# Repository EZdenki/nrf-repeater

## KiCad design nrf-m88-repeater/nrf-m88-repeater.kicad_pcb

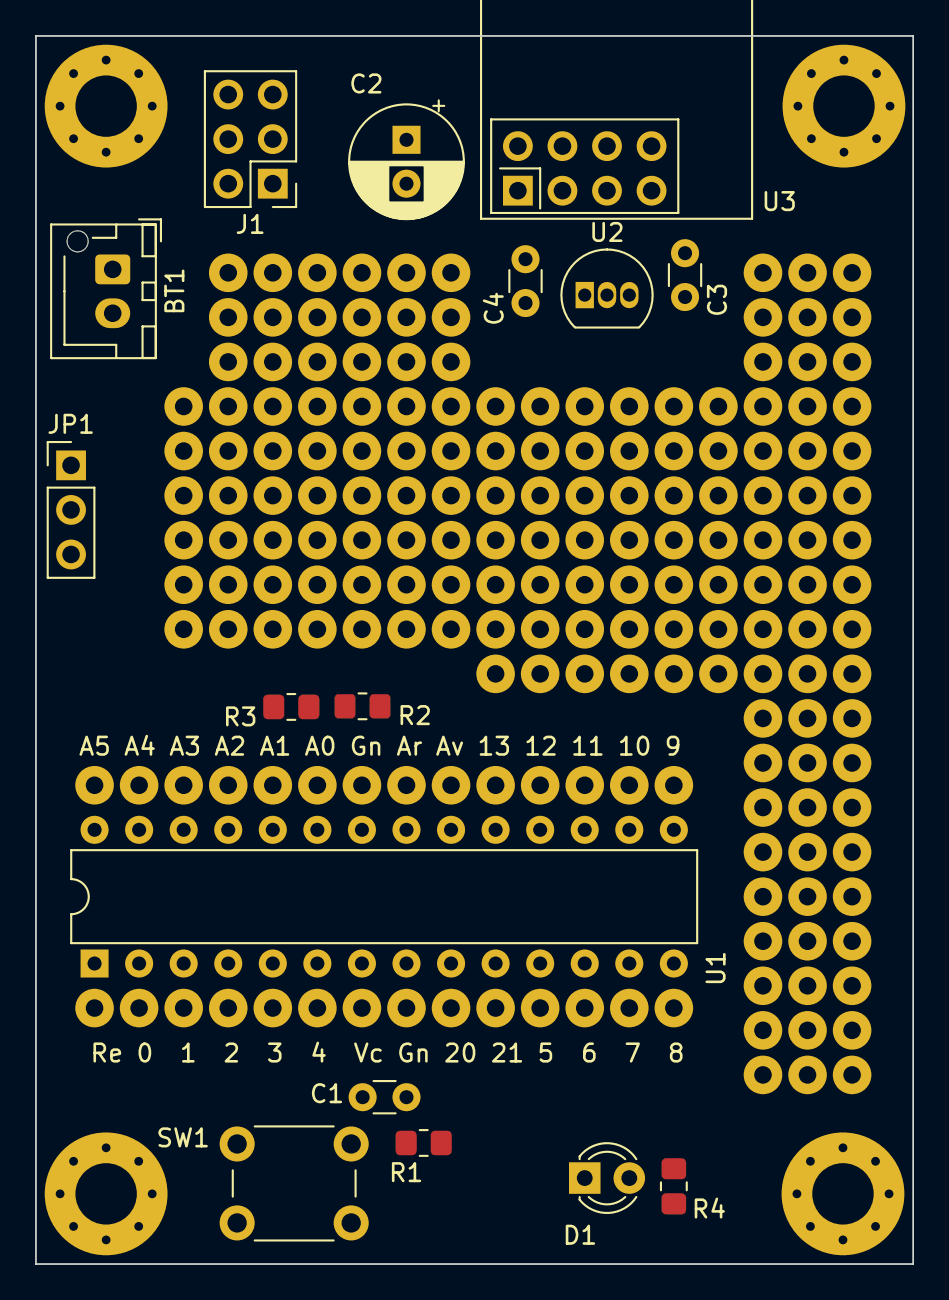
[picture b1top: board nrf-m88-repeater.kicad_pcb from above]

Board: 2 copper layers, 50.0 x 70.0 mm, 20 parts (0 on the bottom side), 13 nets, no tracks yet.

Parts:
BT1: 18650 Battery Holder; JST_XH_B2B-XH-AM_1x02_P2.50mm_Vertical
C1: 100n; C_Disc_D3.0mm_W1.6mm_P2.50mm
C2: 10u; CP_Radial_D6.3mm_P2.50mm
C3: 1u; C_Disc_D3.0mm_W1.6mm_P2.50mm
C4: 2.2u; C_Disc_D3.0mm_W1.6mm_P2.50mm
D1: LED; LED_D3.0mm_FlatTop
H1, H2, H3, H4: MountingHole; MountingHole_3.5mm_Pad_Via
J1: Conn_02x03_Counter_Clockwise; PinHeader_2x03_P2.54mm_Vertical
JP1: PWR Sel.; PinHeader_1x03_P2.54mm_Vertical
R1: 10k; R_0805_2012Metric_Pad1.20x1.40mm_HandSolder
R2: 8.2k; R_0805_2012Metric_Pad1.20x1.40mm_HandSolder
R3: 2.2k; R_0805_2012Metric_Pad1.20x1.40mm_HandSolder
R4: 2k; R_0805_2012Metric_Pad1.20x1.40mm_HandSolder
SW1: RESET; SW_PUSH_6mm
U1: ATmega88; DIP-28_W7.62mm
U2: LP2950-3.3; TO-92_Inline
U3: NRF24L01_Breakout; nRF24L01_Breakout

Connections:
/3.3V: C2.1, C4.2, U2.1 (VO), U3.2 (VCC)
/D8ACT: R4.1, U1.14 (PB0)
/D11MOSI: J1.5, U1.17 (PB3), U3.6 (MOSI)
/D12MISO: J1.1, U1.18 (PB4), U3.7 (MISO)
/D13SCK: J1.2, U1.19 (PB5), U3.5 (SCK)
/D14A0: R2.2, R3.2, U1.23 (PC0)
/ISP_PWR: J1.6, JP1.3 (B)
/RESET: J1.3, SW1.1, U1.1 (~RESET/PC6)
/VCC: C1.1, C3.1, JP1.2 (C), R2.1, U1.7 (VCC), U1.20 (AVCC), U2.3 (VI)
GND: BT1.2 (-), C1.2, C2.2, C3.2, C4.1, D1.1 (K), J1.4, R1.1, R3.1, U1.8 (GND), U1.22 (GND), U2.2 (GND), U3.1 (GND)
unnamed: BT1.1 (+), JP1.1 (A)
unnamed: D1.2 (A), R4.2
unnamed: R1.2, SW1.2

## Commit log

2024-05-07 Ver 1.0
2024-05-08 DIY Version 2
2024-05-13 Repeter V3 Commit
2024-05-22 Added transmitter
2024-05-26 Added V1.3 for Battery monitor
2024-05-26 Fixed up V1.3
2024-05-27 Full Receiver Protoboard V1
2024-05-29 Updated DHT11 wiring
2024-06-14 Updated Receiver V1.2 to add volume and backlight control.
2024-06-14 Added code to toggle LCD backlight when BUT1 pressed
2024-06-15 Added yellow warning LED
2024-06-15 Cleaned wiring
2024-06-15 Updated text, exported png
2024-06-29 Cleaned code, fixed bugs, updated project header file
2024-06-29 Updated nrf-receiver-v1.2.diy
2024-07-01 Updated PIR transmitter, added moisture sensor transmitter
2024-07-02 Fixed battery-monitor voltage divider and other minor bugs.
2024-07-03 Added voltage divider to moisture sensor module. Calibrated moisture sensor battery voltage ADC.
2024-07-03 Added Moisture Sensor Voltage Follower PCB
2024-07-09 Updated DIY files to match actual PCBs
2024-08-17 Updated Generic KiCad Model
